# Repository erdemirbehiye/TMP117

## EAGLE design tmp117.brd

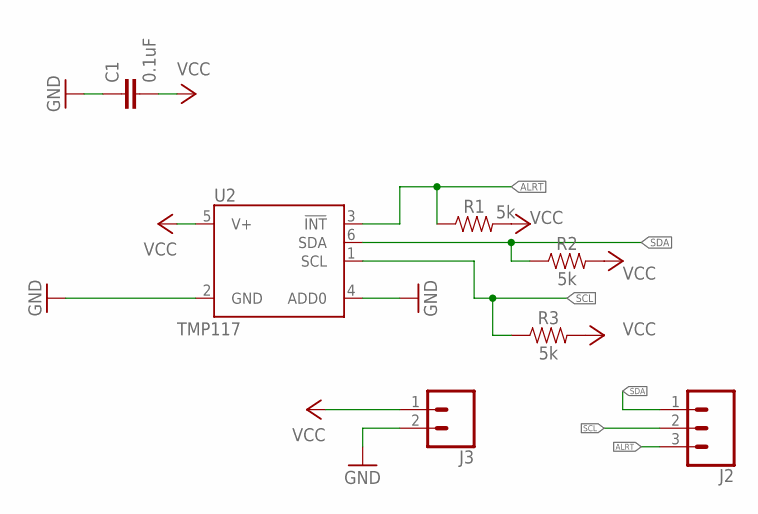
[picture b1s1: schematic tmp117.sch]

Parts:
C1: 0.1uF; 0603
J2: CONN_03; 1X03
J3: CONN_02; 1X02
R1, R2, R3: 5k; 0603
U2: TMP117

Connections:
ALRT: J2.3, R1.1, U2.3 (!INT)
GND: C1.1, J3.2, U2.2 (GND), U2.4 (ADD0)
SCL: J2.2, R3.1, U2.1 (SCL)
SDA: J2.1, R2.1, U2.6 (SDA)
VCC: C1.2, J3.1, R1.2, R2.2, R3.2, U2.5 (V+)

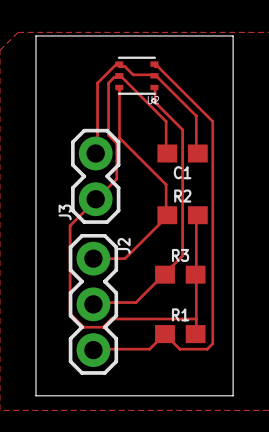
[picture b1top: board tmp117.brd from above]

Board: 2 copper layers, 10.9 x 20.0 mm, 7 parts (0 on the bottom side), 5 nets.

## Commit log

2020-06-17 uploaded test code
2020-06-17 thingspeak connection

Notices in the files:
parts and their libraries:
SparkFun-Capacitors: Licensing: Creative Commons ShareAlike 4.0 International - https://creativecommons.org/licenses/by-sa/4.0
